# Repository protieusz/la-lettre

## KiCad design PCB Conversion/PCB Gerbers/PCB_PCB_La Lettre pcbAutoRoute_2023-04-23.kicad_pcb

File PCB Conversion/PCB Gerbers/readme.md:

La Lettre Gerber zipped file is now release for public.  The current revision for this pcb is REV 3.  PLEASE AT YOUR OWN RISK! I have not send the gerber files to JLCPCB for print yet due to resource contraints.  But the pcb should work.  All tracings were done by EasyEDA auto trace and DRC found no errors.  Please do not come crying to me if the print fails.  You are free to modify or whatever.  I will try to find a way to get the pcb file from EasyEDA since the app uses different method than standard KiCad.  The pcb WILL NOT FIT somepin's La Lettre handwire case file. You will have to modify his step file to fit.  I will include the dxf that was used for the pcb creation.  I may or may not support make revisions or support the improvement of this pcb in the future as this was a request by a friend and my focus is currently on my own designs.

The mcu for my conversion of La Lettre handwire to pcb is Waveshare RP2040 Zero. So Pro Micro will definitely not work unless you mickey mouse handwire to make it work but that's another subject for another time.  As for the firmware https://github.com/protieusz/la-lettre/tree/main/pcb%20firmware the RP2040 version has already been compiled and I have also included the source code if you want to edit.  Good luck to all and have fun.

UPDATE Apr 18, 2023
https://github.com/protieusz/la-lettre/blob/main/PCB%20Conversion/PCB%20Gerbers/Gerber_PCB_La%20Lettre%20pcbLargerpads.zip is Rev 3 and has bigger mcu solder pads for better soldering of the Waveshare RP2040 zero mcu.

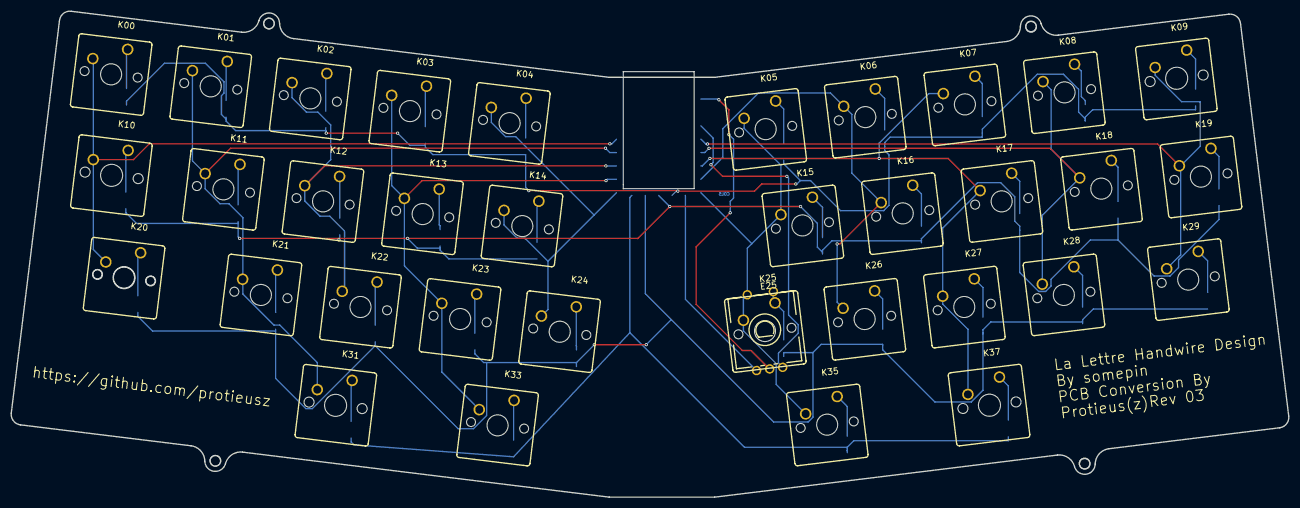
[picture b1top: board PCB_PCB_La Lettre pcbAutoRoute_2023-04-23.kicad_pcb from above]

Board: 2 copper layers, 242.7 x 92.3 mm, 70 parts (0 on the bottom side), 51 nets.

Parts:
D00, D01, D02, D03, D04, D05, D06, D07, D08, D09, D10, D11, D12, D13, D14, D15, D16, D17, D18, D19, D20, D21, D22, D23, D24, D25, D26, D27, D28, D29, D31, D33, D35, D37: DIODE-SOD123
E25: PEC11R-4015F-S0024; SW-TH_PEC11R-4XXXF-SXXXX
K00, K01, K02, K03, K04, K05, K06, K07, K08, K11, K12, K13, K14, K15, K16, K17, K18, K19, K21, K22, K23, K24, K25, K26, K27, K28, K33, K35: Switch; CHERRY_MX_100_MILLMAX
K09, K10, K31, K37: Switch; CHERRY_MX_125_MILLMAX
K20: Switch; CHERRY_MX_175_MILLMAX
K29: Switch; CHERRY_MX_150_MILLMAX
U1: RP2040-ZERO_WAVESHARE - with GPIO; RP2040-ZERO_WAVESHARE- W/ GPIO

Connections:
COL0: K00.2, K10.MX2, K20.MX2, U1.4
COL1: K01.2, K11.2, K21.2, K31.MX2, U1.5
COL2: K02.2, K12.2, K22.2, U1.6
COL3: K03.2, K13.2, K23.2, K33.2, U1.7
COL4: K04.2, K14.2, K24.2, U1.8
COL5: E25.1, K05.2, K15.2, K25.2, K35.2, U1.14
COL6: K06.2, K16.2, K26.2, U1.15
COL7: K07.2, K17.2, K27.2, K37.MX2, U1.16
COL8: K08.2, K18.2, K28.2, U1.17
COL9: K09.MX2, K19.2, K29.2, U1.18
D00_A: D00.A, K00.1
D03_A: D03.A, K03.1
D05_A: D05.A, K05.1
D07_A: D07.A, K07.1
D09_A: D09.A, K09.MX1
D11_A: D11.A, K11.1
D12_A: D12.A, K12.1
D14_A: D14.A, K14.1
D16_A: D16.A, K16.1
D18_A: D18.A, K18.1
D21_A: D21.A, K21.1
D22_A: D22.A, K22.1
D24_A: D24.A, K24.1
D25_A: D25.A, E25.2, K25.1
D26_A: D26.A, K26.1
D28_A: D28.A, K28.1
D33_A: D33.A, K33.1
D35_A: D35.A, K35.1
D37_A: D37.A, K37.MX1
ENCA: E25.A, U1.13
ENCB: E25.B, U1.19
GND: E25.C, U1.21
K01_1: D01.A, K01.1
K02_1: D02.A, K02.1
K04_1: D04.A, K04.1
K06_1: D06.A, K06.1
K08_1: D08.A, K08.1
K10_MX1: D10.A, K10.MX1
K13_1: D13.A, K13.1
K15_1: D15.A, K15.1
K17_1: D17.A, K17.1
K19_1: D19.A, K19.1
K20_MX1: D20.A, K20.MX1
K23_1: D23.A, K23.1
K27_1: D27.A, K27.1
K29_1: D29.A, K29.1
K31_MX1: D31.A, K31.MX1
ROW0: D00.C, D01.C, D02.C, D03.C, D04.C, D05.C, D06.C, D07.C, D08.C, D09.C, U1.12
ROW1: D10.C, D11.C, D12.C, D13.C, D14.C, D15.C, D16.C, D17.C, D18.C, D19.C, U1.11
ROW2: D20.C, D21.C, D22.C, D23.C, D24.C, D25.C, D26.C, D27.C, D28.C, D29.C, U1.10
ROW3: D31.C, D33.C, D35.C, D37.C, U1.9

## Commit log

2023-04-11 Added pcb preview and readme
2023-04-11 Add 1 preview pic
2023-04-11 Changed the folder name to make pic showup
2023-04-11 change 2
2023-04-11 Upload pics
2023-04-11 Removed pic
2023-04-11 Remove pic
2023-04-11 All a title to readme
2023-04-11 Grammar edit
2023-04-11 Add link to somepin's page
2023-04-12 Add pcb firmware
2023-04-12 added double tap reset and combo enable setting
2023-04-12 Added compiled uf2 file
2023-04-17 Release gerbers for public rev 2
2023-04-17 Add readme
2023-04-17 add the firmware link
2023-04-17 Add rev 2 pics
2023-04-18 Increase mcu solder pads size
2023-04-18 Update info about REV 3
2023-04-19 Update mistake on Rev #
2023-04-23 Uploaded converted EasyEDA json to Kicad pcb file
